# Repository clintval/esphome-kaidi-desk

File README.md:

# esphome-kaidi-desk

Control a Kaidi standing desk from Home Assistant with an ESP32 and ESPHome.

## Introduction

Many budget electric standing desks, sit-stand desks and desk frames run on a control box from Kaidi (Changzhou Kaidi Electrical), such as the `KDDY094`, which talks to its keypad over 9600 baud serial on a 10-pin RJ50 cable.
This component reads the desk's height and moves it the way the keypad does, including the reset that clears E04.

To check your desk, look for a `KAIDI` label and a `KDDY` model number on the control box under the desktop.

| Desk | Control box | Status |
| --- | --- | --- |
| ApexDesk K Series 3-stage dual-motor desk base | `KDDY094` | Tested |
| Other desks with a `KDDY094` box (variants S500, S650 and S663) | `KDDY094` | Expected to work |
| Lazy Maisons desk (2021) with a `KDH170-311` keypad | `KDDY094`, S440, `DY094-409/000838A 06-V2.5` | Expected to work: [`yog18r/kaidi-desk-esphome`](https://github.com/yog18r/kaidi-desk-esphome) measured the same contacts and frames, but this dongle hasn't been tried on it; set the target height's `max_value` to 44 cm (17.3 in) |
| Desks with a `KDDY041` box and `KD1869A` keypad | `KDDY041` | Same protocol, but an 8-pin cable, so the dongle won't fit |

If your desk works, please open an issue or pull request to add it.

## Quick Start

With an assembled board, open the [browser installer](https://clintval.github.io/esphome-kaidi-desk/) in Chrome or Edge, plug in its USB-C and follow the steps. It goes live with the first release.
The prebuilt firmware holds no secrets: Wi-Fi is set over USB, Home Assistant sets the encryption key within 15 minutes of power-up, and updates only come over HTTPS from this repository's releases.

To build your own firmware instead, use the component in an ESPHome config, wired as in [Hardware](#hardware):

```yaml
external_components:
  - source: github://clintval/esphome-kaidi-desk@main
    components: [kaidi_desk]

uart:
  - id: desk_uart
    rx_pin: GPIO4
    tx_pin: GPIO7
    baud_rate: 9600
  - id: keypad_uart
    rx_pin: GPIO3
    baud_rate: 9600

kaidi_desk:
  uart_id: desk_uart
  keypad_uart_id: keypad_uart
  tx_enable_pin: GPIO6
  wake_pin: GPIO10
  keypad_cutoff_pin: GPIO1

sensor:
  - platform: kaidi_desk
    height:
      name: Height

number:
  - platform: kaidi_desk
    target_height:
      name: Target Height
      unit_of_measurement: in
```

A complete config is in [`example/kaidi-desk.yaml`](example/kaidi-desk.yaml), which takes the board and every entity from [`example/desk.yaml`](example/desk.yaml).
It transmits at reduced Wi-Fi power (`output_power: 8.5dB`), which is easier on the desk's 5 V supply; some ESP32-C3 boards can't connect at full power. Raise it if the desk is far from your router.
It encrypts the Home Assistant connection and Wi-Fi updates with one key, and puts a password on the fallback hotspot. Add `wifi_ssid`, `wifi_password`, `ap_password` and `api_encryption_key` to your `secrets.yaml`; the `openssl rand -base64 32` command makes a key.

## Entities

| Platform | Key | Purpose |
| --- | --- | --- |
| `sensor` | `height` | Height above the desk's lowest point, in cm (Home Assistant converts units) |
| `text_sensor` | `status` | `Ready`, `Reset Needed` (E04), `Resetting`, `Keypad Settings`, or `Asleep` |
| `text_sensor` | `last_stop` | Why the last move ended, such as `Reached target`, `Reached preset 2`, `Stopped`, `Stopped short at a limit or obstruction` `Keypad took over` or `Lost the height`; also the result of a preset save, and what the keypad did, such as `Keypad moved the desk up`, `Keypad went to preset 2` or `Keypad saved preset 3` |
| `text_sensor` | `keypad` | What the keypad is doing: `Asleep`, `Awake`, `Up`, `Down`, `Preset 1` to `Preset 4`, or `Reset`; needs `keypad_uart_id` |
| `number` | `target_height` | Move to a height; follows the real height while idle, in `cm` or `in` |
| `button` | `nudge_up`, `nudge_down` | Move briefly up or down, about half an inch |
| `button` | `stop` | Stop any move |
| `button` | `preset_1` to `preset_4` | Go to a position saved on the keypad; the box drives there and stops by itself |
| `button` | `save_preset_1` to `save_preset_4` | Replace a preset with the current height, once the desk is still; the box sends no confirmation, and presets can't be read back |
| `button` | `reset` | Hold Up and Down until the box re-zeros, which clears E04; it ignores other moves until it finishes, and may clear the keypad's presets |
| `switch` | `keep_awake` | Hold the wake line high and send an Idle frame every 4 s, inside the box's 10 to 12 s sleep timer, so the box stays awake, height streams live and moves start at once |

## Hardware

> [!WARNING]
> This board is untested: none has been built yet, and the desk-power test and a check of the jacks' contact order are still pending, so don't order boards from it yet.
> The protoboard build, under "Build without a PCB" below, is tested and works.

The dongle sits inline: the keypad plugs into one end, and a short cable runs from the other end to the control box.
A 74AHCT125 drives the box only while the ESP is sending, so the keypad keeps working if the ESP is unpowered, resetting or unplugged.
The ESP also decodes what the keypad sends, and keeps listening while it cuts the keypad off, so a keypad press takes over from a Home Assistant move at once.
Power comes from the desk by default. USB-C is for flashing and for desks that can't supply the ESP, and it is isolated, so any charger or computer can stay plugged in.

<details>
<summary>Schematic</summary>

</details>

| RJ50 contact | Signal | Path |
| --- | --- | --- |
| 2 | +5 V | Straight through; also powers the 74AHCT125 and, through JP1, the ESP |
| 3 | Ground | Straight through |
| 7 | Command, keypad to box | Keypad through switch U9 and 1 kΩ; gate A drives the box side through 47 Ω from GPIO7 when GPIO6 is high. GPIO1 high opens U9 and cuts the keypad off; a shunt on JP2 bypasses U9 |
| 8 | Height, box to keypad | Straight through; 100 kΩ over 150 kΩ to GPIO4 |
| 10 | Wake, keypad to box | Keypad through 1 kΩ; gate B drives the box side high through 47 Ω when GPIO10 is high |
| 1, 4, 5, 6, 9 | Unused by this dongle | Straight through |

The board is an 84 × 50 mm, four-layer KiCad design in [`hardware/`](hardware), made to be assembled by a board house.
Every part is fitted by the board house, including the jacks, whose metal shells are tied to the desk's ground and sit flush with the box.

| Situation | Protection |
| --- | --- |
| Two-prong charger or noisy dock leaking mains AC, which makes touch keypads barely register a press | USB-C power (B0505S-2WR3) and data (ADuM3160) both cross isolation barriers, with a 3 mm moat on all four layers |
| Weak desk 5 V | 1000 µF reserve; otherwise pull JP1 and use USB-C |
| Desk and USB-C connected together | One Schottky diode each, so neither feeds back into the other |
| Short circuit on the board | Resettable fuses on the desk (F1) and USB-C (F2) supplies; F1 doesn't cover the keypad's own straight-through 5 V |
| USB hot-plug spikes and converter light load, which the B0505S-2WR3 isn't rated for | Surge clamp D4 at its input and preload R14 at its output |
| Static on the cables | SRV05-4 clamps at both jacks and a USBLC6-2 at USB-C |
| ESP crash, reset or power loss | Pull-downs turn the drivers off and reconnect the keypad, and ESPHome's watchdog restarts a hung ESP |
| ESP and keypad driving the box at once | U9 cuts the keypad off during a move, and the ESP still listens to it; 1 kΩ and 47 Ω limit the current otherwise |

It can't protect against a fault in the control box, the keypad or the cable, and it relies on the box's own anti-collision stop.
The isolation keeps grounds apart; it is not a safety barrier against mains.

<details>
<summary>Build without a PCB</summary>

The protoboard build is the same circuit hand-built on a 1.5 × 2 in EPLZON solderable breadboard, with a Bipom BRK10P10CSJ breakout for the keypad and a cut 10P10C cable to the desk.

> [!IMPORTANT]
> Power the protoboard build from a grounded (three-prong) USB charger, a computer's USB port or a power bank.
> It has no isolated power input, so a two-prong charger leaks a little mains AC onto the desk's ground and touch-sensitive keypads barely register a press.

On this build, configure `tx_enable_pin: GPIO6`, `wake_pin: GPIO0` and `rx_pin: GPIO3`, and leave out `keypad_uart_id`, `keypad_cutoff_pin` and the second uart.

</details>

## Enclosure

A two-part, 89 × 55 × 24 mm box is in [`hardware/enclosure/`](hardware/enclosure) as STEP and STL, sized to sit in the desk's cable tray beside the control box.
The USB-C opening is on the long side. RESET, BOOT and JP1 are inside.

Press the two heat-set inserts into the base with a soldering iron at about 220 °C, set the board on its posts, and screw the lid down with two M3 × 20 mm socket-head cap screws, which sit flush in the lid.
Print it in MJF nylon or, at home, PETG; resin tends to crack around the inserts.

## Bill of Materials

| Qty | Part | Where to order |
| --- | --- | --- |
| 1 | PCB, 84 × 50 mm, 4 layers, 1.6 mm, all parts fitted on the top side | [JLCPCB](https://jlcpcb.com/): upload [`kaidi-desk-gerbers.zip`](hardware/kaidi-desk-gerbers.zip), then [`kaidi-desk-bom.csv`](hardware/kaidi-desk-bom.csv) and [`kaidi-desk-positions.csv`](hardware/kaidi-desk-positions.csv) |
| 1 | Enclosure base and lid, MJF nylon (PA12) | [JLCPCB 3D printing](https://jlcpcb.com/3d-printing): upload [`base.stl`](hardware/enclosure/base.stl) and [`lid.stl`](hardware/enclosure/lid.stl) |
| 1 | Jumper shunt, 2.54 mm (JP1) | Any |
| 1 | RJ50 (10P10C) cable, about 1 ft, wired straight through, dongle to control box | [Winford CBM10R1TS-1](https://www.winford.com/products/cbm10.php) (US) or [Delock 80185](https://www.delock.com/produkt/80185/merkmale.html) (EU) |
| 2 | M3 × 20 mm socket-head cap screw, ISO 4762 | [Amazon](https://www.amazon.com/s?k=M3x20+socket+head+cap+screw+ISO+4762+stainless) |
| 2 | M3 heat-set insert, 5.7 mm long, 4.0 mm hole (ruthex M3) | [Amazon](https://www.amazon.com/s?k=ruthex+M3+heat+set+inserts) |

The parts the board house fits are listed in [`scripts/parts.py`](scripts/parts.py) with their LCSC numbers.
In the assembly preview, check the rotation of every chip, diode, LED and C4 before ordering: board houses often rotate parts differently from KiCad.

The cable must be wired straight through; flat telephone-style 10P10C cables are often reversed.

## Protocol

Each frame is 7 bytes, `0x68 0x01 <mode> <hi> <lo> <checksum> 0x16`, where the checksum is the low byte of `0x01 + mode + hi + lo`.

| Direction | Mode | Meaning |
| --- | --- | --- |
| Keypad to box | `0x01` | Up |
| Keypad to box | `0x02` | Down |
| Keypad to box | `0x03` | Idle |
| Keypad to box | `0x04` | Up and Down held (reset) |
| Keypad to box | `0x06` to `0x09` | Go to preset 1 to 4, repeated until the box stops; the height bytes are zero |
| Keypad to box | `0x0A`, `0x0B`, `0x0C`, `0x17` | Save the current height as preset 1 to 4, sent once |
| Box to keypad | `0x00` | Height in 0.1 cm |
| Box to keypad | `0x30` | Reset needed (E04); the value counts down during the reset |
| Box to keypad | `0x04` | Reset rebound in progress |
| Box to keypad | `0x62` | Keypad settings open; the value is the setting, not a height |

The keypad sends a frame every 14 ms while awake, and the box needs about 1.5 s after waking before it accepts a move.
The box sends a height about every 22 ms while awake and for 10 to 12 s after the wake line drops.
E04 means a reset was released before the rebound. Releasing one early can damage the motor, so leave it to finish.

## Development and Testing

See the [contributing guide](./CONTRIBUTING.md) for more information.

## Acknowledgements

The frame format was first decoded in [`xvzf/kaidi-desk-controller-protocol`](https://github.com/xvzf/kaidi-desk-controller-protocol), and [`jcappaert/esphome-kaidi`](https://github.com/jcappaert/esphome-kaidi) read the height on the same `KDDY094` box.
The preset commands were documented by [`yog18r/kaidi-desk-esphome`](https://github.com/yog18r/kaidi-desk-esphome), a separate desk-powered board for the same box.

## License

MIT

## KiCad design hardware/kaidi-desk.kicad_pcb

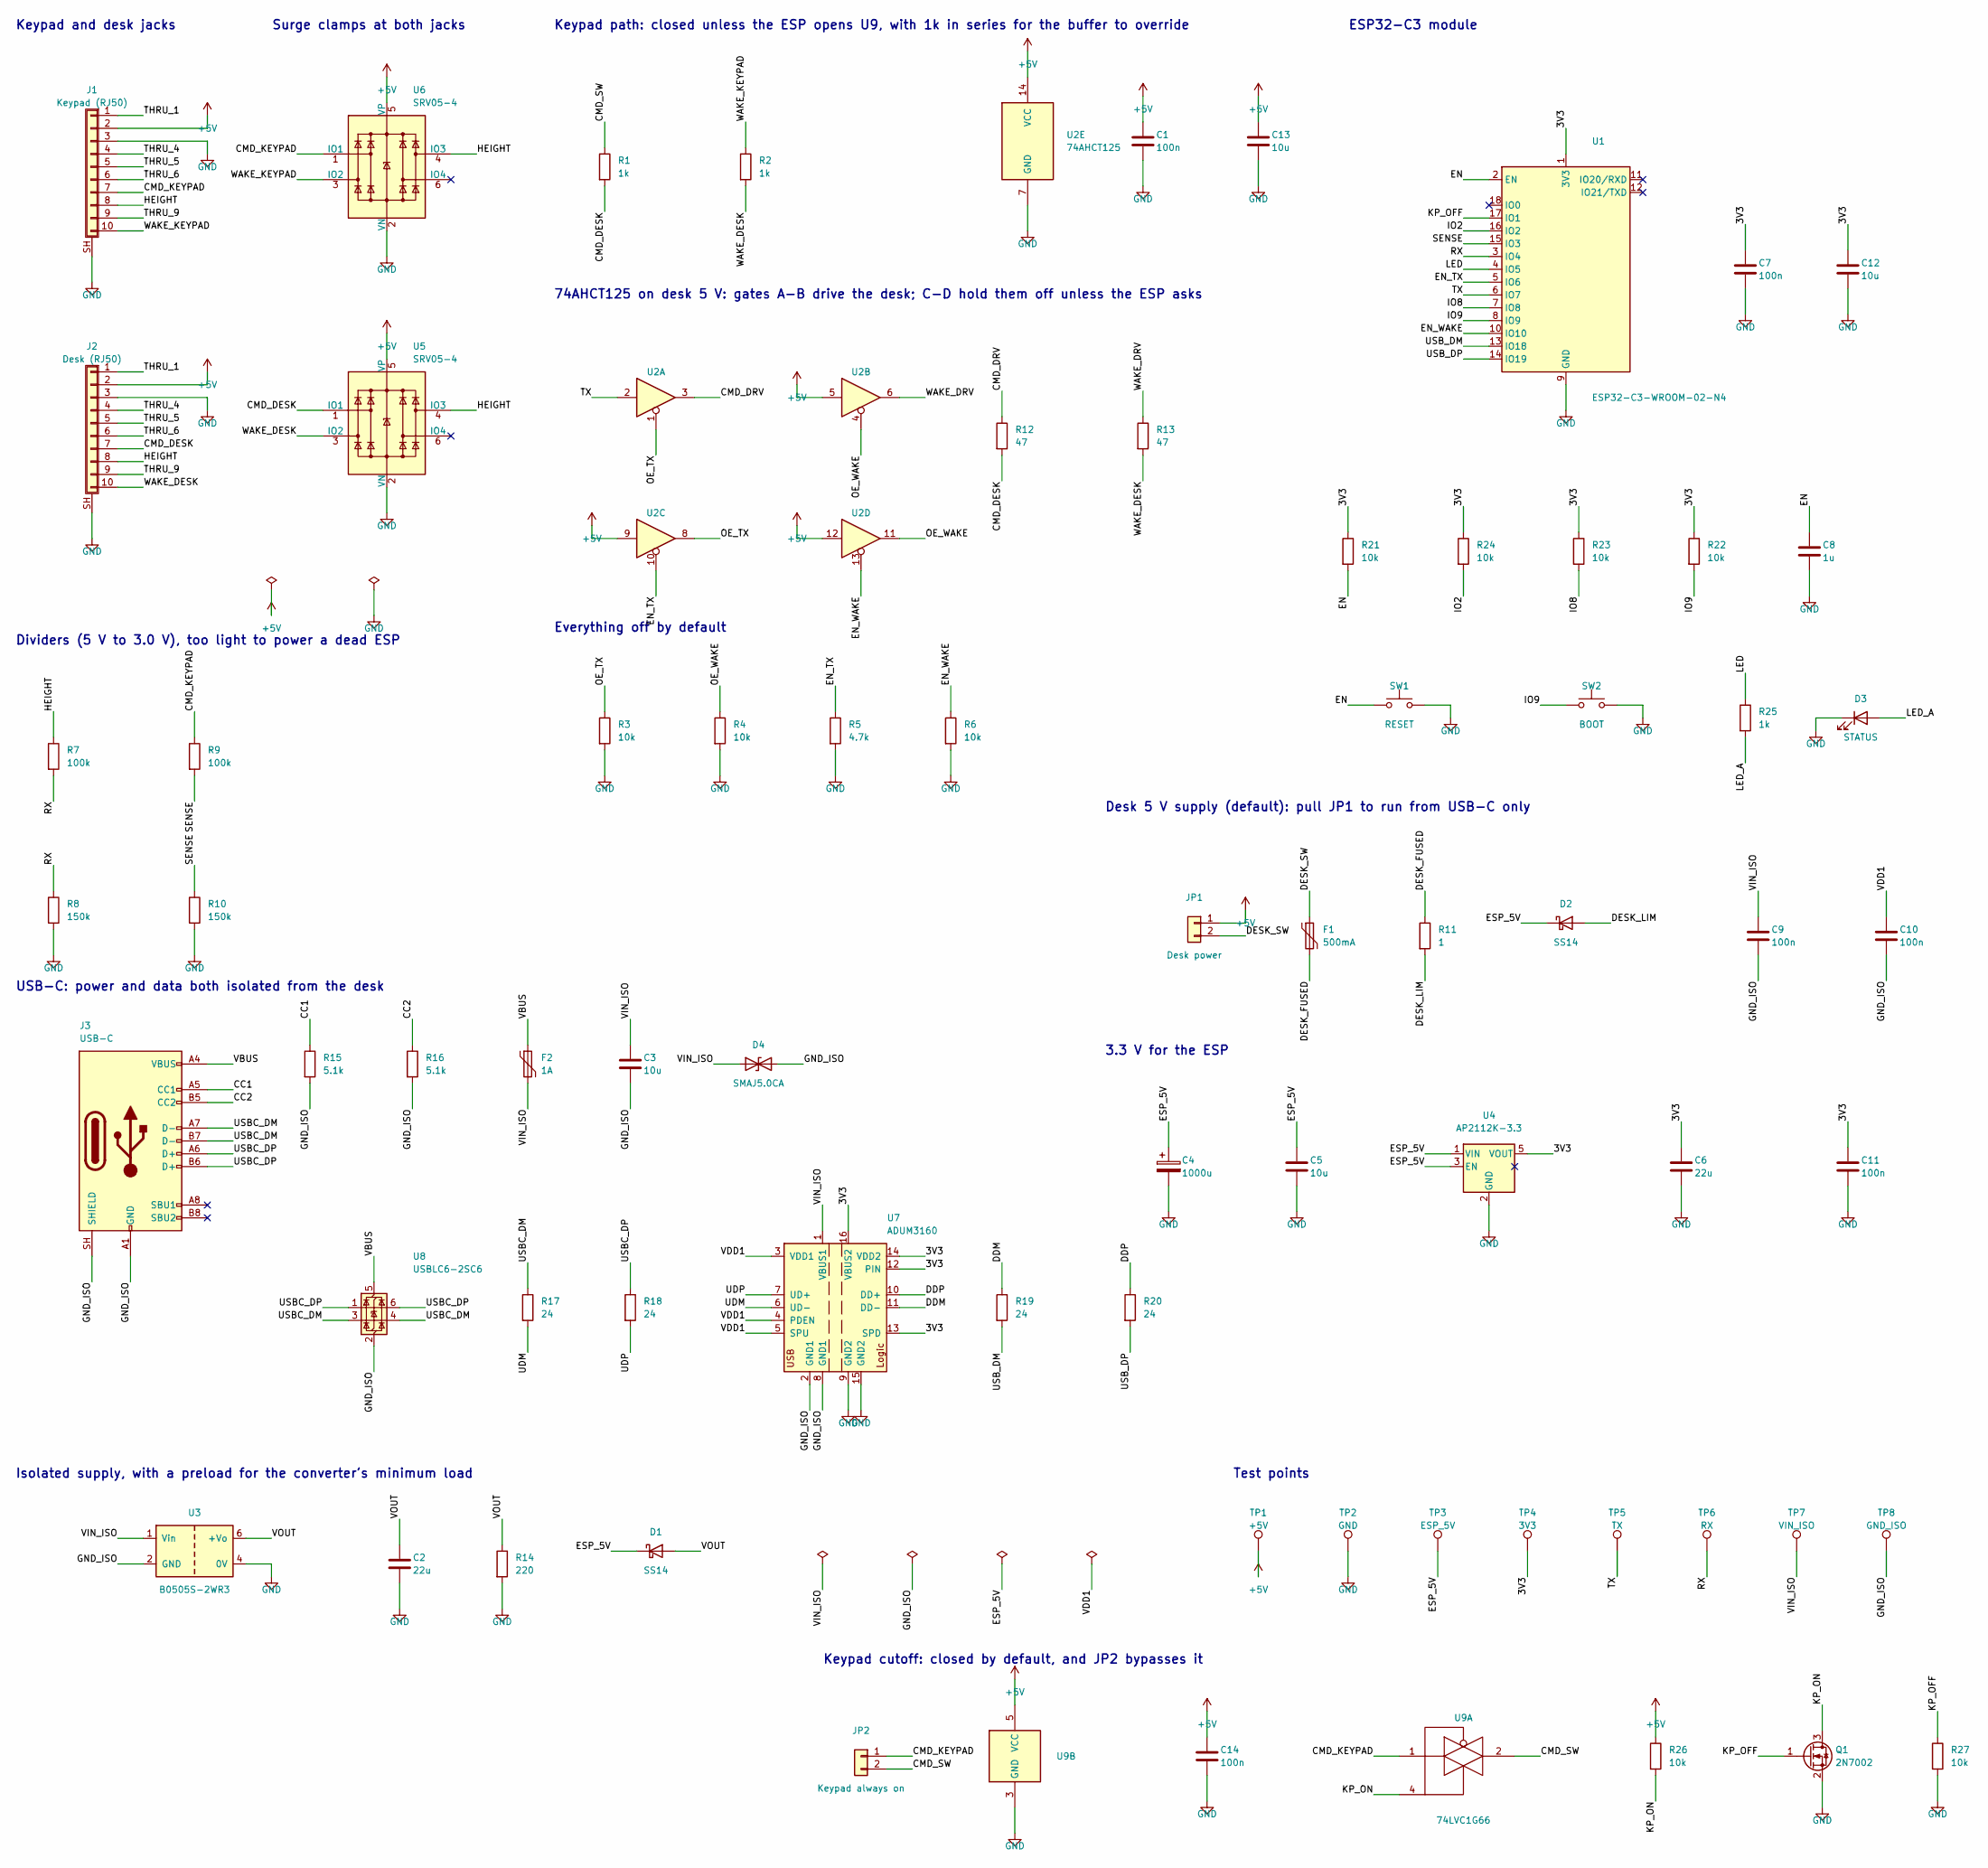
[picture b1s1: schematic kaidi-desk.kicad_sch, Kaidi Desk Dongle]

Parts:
C1, C7, C9, C10, C11, C14: 100n; C_0603_1608Metric
C2: 22u; C_1206_3216Metric
C3, C5, C12, C13: 10u; C_0805_2012Metric
C4: 1000u; CP_Elec_10x10.5
C6: 22u; C_0805_2012Metric
C8: 1u; C_0603_1608Metric
D1, D2: SS14; D_SMA
D3: STATUS; LED_0603_1608Metric
D4: SMAJ5.0CA; D_SMA
F1: 500mA; Fuse_1206_3216Metric
F2: 1A; Fuse_1206_3216Metric
J1: Keypad (RJ50); RJ50_TE_5558067-1_Horizontal
J2: Desk (RJ50); RJ50_TE_5558067-1_Horizontal
J3: USB-C; USB_C_Receptacle_HRO_TYPE-C-31-M-12
JP1: Desk power; PinHeader_1x02_P2.54mm_Vertical
JP2: Keypad always on; PinHeader_1x02_P2.54mm_Vertical
Q1: 2N7002; SOT-23
R1, R2, R25: 1k; R_0603_1608Metric
R3, R4, R6, R21, R22, R23, R24, R26, R27: 10k; R_0603_1608Metric
R5: 4.7k; R_0603_1608Metric
R7, R9: 100k; R_0603_1608Metric
R8, R10: 150k; R_0603_1608Metric
R11: 1; R_1206_3216Metric
R12, R13: 47; R_0603_1608Metric
R14: 220; R_1206_3216Metric
R15, R16: 5.1k; R_0603_1608Metric
R17, R18, R19, R20: 24; R_0603_1608Metric
SW1: RESET; SW_Push_1P1T_XKB_TS-1187A
SW2: BOOT; SW_Push_1P1T_XKB_TS-1187A
TP1: +5V; TestPoint_Pad_D1.5mm
TP2: GND; TestPoint_Pad_D1.5mm
TP3: ESP_5V; TestPoint_Pad_D1.5mm
TP4: 3V3; TestPoint_Pad_D1.5mm
TP5: TX; TestPoint_Pad_D1.5mm
TP6: RX; TestPoint_Pad_D1.5mm
TP7: VIN_ISO; TestPoint_Pad_D1.5mm
TP8: GND_ISO; TestPoint_Pad_D1.5mm
U1: ESP32-C3-WROOM-02-N4; ESP32-C3-WROOM-02
U2: 74AHCT125; SOIC-14_3.9x8.7mm_P1.27mm
U3: B0505S-2WR3; Converter_DCDC_Mornsun_B_S-2WR3_SIP
U4: AP2112K-3.3; SOT-23-5
U5, U6: SRV05-4; SOT-23-6
U7: ADUM3160; SOIC-16W_7.5x10.3mm_P1.27mm
U8: USBLC6-2SC6; SOT-23-6
U9: 74LVC1G66; SOT-23-5

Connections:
+5V: C1.1, C13.1, C14.1, J1.2, J2.2, JP1.1, R26.1, TP1.1, U2.5, U2.9, U2.12, U2.14 (VCC), U5.5 (VP), U6.5 (VP), U9.5 (VCC)
/3V3: C6.1, C7.1, C11.1, C12.1, R21.1, R22.1, R23.1, R24.1, TP4.1, U1.1 (3V3), U4.5 (VOUT), U7.12 (PIN), U7.13 (SPD), U7.14 (VDD2), U7.16 (VBUS2)
/CC1: J3.A5 (CC1), R15.1
/CC2: J3.B5 (CC2), R16.1
/CMD_DESK: J2.7, R1.2, R12.2, U5.1 (IO1)
/CMD_DRV: R12.1, U2.3
/CMD_KEYPAD: J1.7, JP2.1, R9.1, U6.1 (IO1), U9.1
/CMD_SW: JP2.2, R1.1, U9.2
/DDM: R19.1, U7.11 (DD-)
/DDP: R20.1, U7.10 (DD+)
/DESK_FUSED: F1.2, R11.1
/DESK_LIM: D2.2 (A), R11.2
/DESK_SW: F1.1, JP1.2
/EN: C8.1, R21.2, SW1.1, U1.2 (EN)
/EN_TX: R5.1, U1.5 (IO6), U2.10
/EN_WAKE: R6.1, U1.10 (IO10), U2.13
/ESP_5V: C4.1, C5.1, D1.1 (K), D2.1 (K), TP3.1, U4.1 (VIN), U4.3 (EN)
/GND_ISO: C3.2, C9.2, C10.2, D4.2 (A2), J3.A1 (GND), J3.A12 (GND), J3.B1 (GND), J3.B12 (GND), J3.SH (SHIELD), R15.2, R16.2, TP8.1, U3.2 (GND), U7.2 (GND1), U7.8 (GND1), U8.2 (GND)
/HEIGHT: J1.8, J2.8, R7.1, U5.4 (IO3), U6.4 (IO3)
/IO2: R24.2, U1.16 (IO2)
/IO8: R23.2, U1.7 (IO8)
/IO9: R22.2, SW2.1, U1.8 (IO9)
/KP_OFF: Q1.1 (G), R27.1, U1.17 (IO1)
/KP_ON: Q1.3 (D), R26.2, U9.4
/LED: R25.1, U1.4 (IO5)
/LED_A: D3.2 (A), R25.2
/OE_TX: R3.1, U2.1, U2.8
/OE_WAKE: R4.1, U2.4, U2.11
/RX: R7.2, R8.1, TP6.1, U1.3 (IO4)
/SENSE: R9.2, R10.1, U1.15 (IO3)
/THRU_1: J1.1, J2.1
/THRU_4: J1.4, J2.4
/THRU_5: J1.5, J2.5
/THRU_6: J1.6, J2.6
/THRU_9: J1.9, J2.9
/TX: TP5.1, U1.6 (IO7), U2.2
/UDM: R17.2, U7.6 (UD-)
/UDP: R18.2, U7.7 (UD+)
/USBC_DM: J3.A7 (D-), J3.B7 (D-), R17.1, U8.3 (I/O2), U8.4 (I/O2)
/USBC_DP: J3.A6 (D+), J3.B6 (D+), R18.1, U8.1 (I/O1), U8.6 (I/O1)
/USB_DM: R19.2, U1.13 (IO18)
/USB_DP: R20.2, U1.14 (IO19)
/VBUS: F2.1, J3.A4 (VBUS), J3.A9 (VBUS), J3.B4 (VBUS), J3.B9 (VBUS), U8.5 (VBUS)
/VDD1: C10.1, U7.3 (VDD1), U7.4 (PDEN), U7.5 (SPU)
/VIN_ISO: C3.1, C9.1, D4.1 (A1), F2.2, TP7.1, U3.1 (Vin), U7.1 (VBUS1)
/VOUT: C2.1, D1.2 (A), R14.1, U3.6 (+Vo)
/WAKE_DESK: J2.10, R2.2, R13.2, U5.3 (IO2)
/WAKE_DRV: R13.1, U2.6
/WAKE_KEYPAD: J1.10, R2.1, U6.3 (IO2)
GND: C1.2, C2.2, C4.2, C5.2, C6.2, C7.2, C8.2, C11.2, C12.2, C13.2, C14.2, D3.1 (K), J1.3, J1.SH (Shield), J2.3, J2.SH (Shield), Q1.2 (S), R3.2, R4.2, R5.2, R6.2, R8.2, R10.2, R14.2, R27.2, SW1.2, SW2.2, TP2.1, U1.9 (GND), U1.19 (GND), U2.7 (GND), U3.4 (0V), U4.2 (GND), U5.2 (VN), U6.2 (VN), U7.9 (GND2), U7.15 (GND2), U9.3 (GND)

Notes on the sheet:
Keypad and desk jacks
Surge clamps at both jacks
Keypad path: closed unless the ESP opens U9, with 1k in series for the buffer to override
74AHCT125 on desk 5 V: gates A-B drive the desk; C-D hold them off unless the ESP asks
Everything off by default
Keypad cutoff: closed by default, and JP2 bypasses it
Dividers (5 V to 3.0 V), too light to power a dead ESP
ESP32-C3 module
Desk 5 V supply (default): pull JP1 to run from USB-C only
3.3 V for the ESP
USB-C: power and data both isolated from the desk
Isolated supply, with a preload for the converter's minimum load
Test points

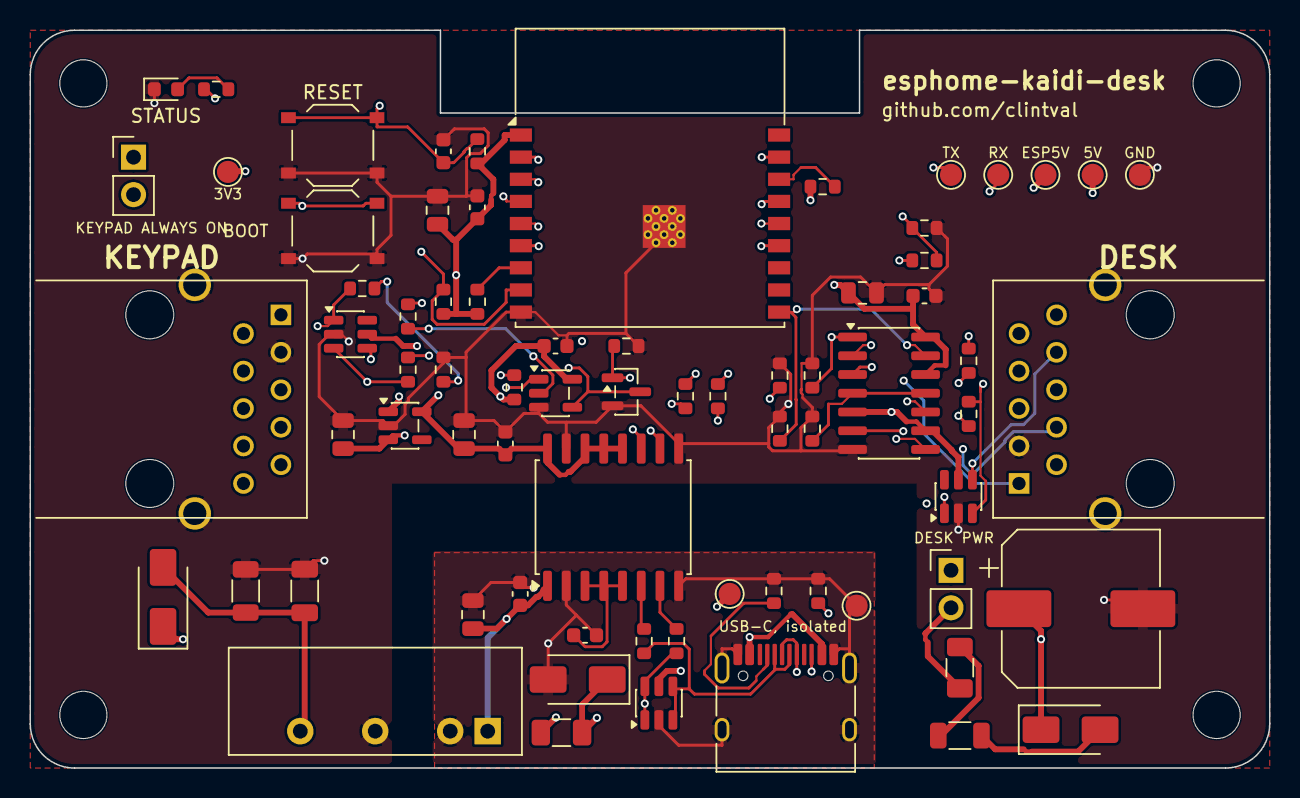
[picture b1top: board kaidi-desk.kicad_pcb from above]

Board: 4 copper layers, 84.0 x 50.0 mm, 72 parts (0 on the bottom side), 50 nets.

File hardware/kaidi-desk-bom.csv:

Comment,Designator,Footprint,LCSC Part #
100 nF 50 V X7R 0603,"C1,C7,C9,C10,C11,C14",C_0603_1608Metric,C14663
22 uF 25 V X5R 1206,C2,C_1206_3216Metric,C12891
10 uF 25 V X5R 0805,"C3,C5,C12,C13",C_0805_2012Metric,C15850
"1000 uF 10 V electrolytic, 10 x 10.5 mm, VT1A102MG105000CE0",C4,CP_Elec_10x10.5,C190288
22 uF 25 V X5R 0805,C6,C_0805_2012Metric,C45783
1 uF 50 V X5R 0603,C8,C_0603_1608Metric,C15849
"SS14 Schottky, SMA","D1,D2",D_SMA,C2480
"Green LED 0603, KT-0603G",D3,LED_0603_1608Metric,C12624
"SMAJ5.0CA surge clamp, SMA",D4,D_SMA,C83324
"500 mA resettable fuse 1206, 1206L050/33NR",F1,Fuse_1206_3216Metric,C19193043
"1 A resettable fuse 1206, 1206L100/24NR",F2,Fuse_1206_3216Metric,C7542957
"Shielded 10P10C jack, TE 5558067-1","J1,J2",RJ50_TE_5558067-1_Horizontal,C306018
"USB-C receptacle, TYPE-C-31-M-12",J3,USB_C_Receptacle_HRO_TYPE-C-31-M-12,C165948
"1 x 2 pin header 2.54 mm, PZ254V-11-02P","JP1,JP2",PinHeader_1x02_P2.54mm_Vertical,C492401
"2N7002, SOT-23",Q1,SOT-23,C8545
1 k 1% 0603,"R1,R2,R25",R_0603_1608Metric,C21190
10 k 1% 0603,"R3,R4,R6,R21,R22,R23,R24,R26,R27",R_0603_1608Metric,C25804
4.7 k 1% 0603,R5,R_0603_1608Metric,C23162
100 k 1% 0603,"R7,R9",R_0603_1608Metric,C25803
150 k 1% 0603,"R8,R10",R_0603_1608Metric,C22807
1 ohm 1% 1206,R11,R_1206_3216Metric,C17928
47 ohm 1% 0603,"R12,R13",R_0603_1608Metric,C23182
"220 ohm 0.5 W 1206, HP06W2J0221T5E",R14,R_1206_3216Metric,C2759071
5.1 k 1% 0603,"R15,R16",R_0603_1608Metric,C23186
24 ohm 1% 0603,"R17,R18,R19,R20",R_0603_1608Metric,C4198
"Push button, TS-1187A-B-A-B","SW1,SW2",SW_Push_1P1T_XKB_TS-1187A,C318884
ESP32-C3-WROOM-02-N4,U1,ESP32-C3-WROOM-02,C2934560
"SN74AHCT125DR, SOIC-14",U2,SOIC-14_3.9x8.7mm_P1.27mm,C155176
"B0505S-2WR3 isolated converter, SIP",U3,Converter_DCDC_Mornsun_B_S-2WR3_SIP,C7465195
"AP2112K-3.3TRG1, SOT-23-5",U4,SOT-23-5,C51118
"SRV05-4, SOT-23-6","U5,U6",SOT-23-6,C2985619
"ADUM3160BRWZ, SOIC-16W",U7,SOIC-16W_7.5x10.3mm_P1.27mm,C108501
"USBLC6-2SC6, SOT-23-6",U8,SOT-23-6,C7519
"SN74LVC1G66DBVR, SOT-23-5",U9,SOT-23-5,C133643
